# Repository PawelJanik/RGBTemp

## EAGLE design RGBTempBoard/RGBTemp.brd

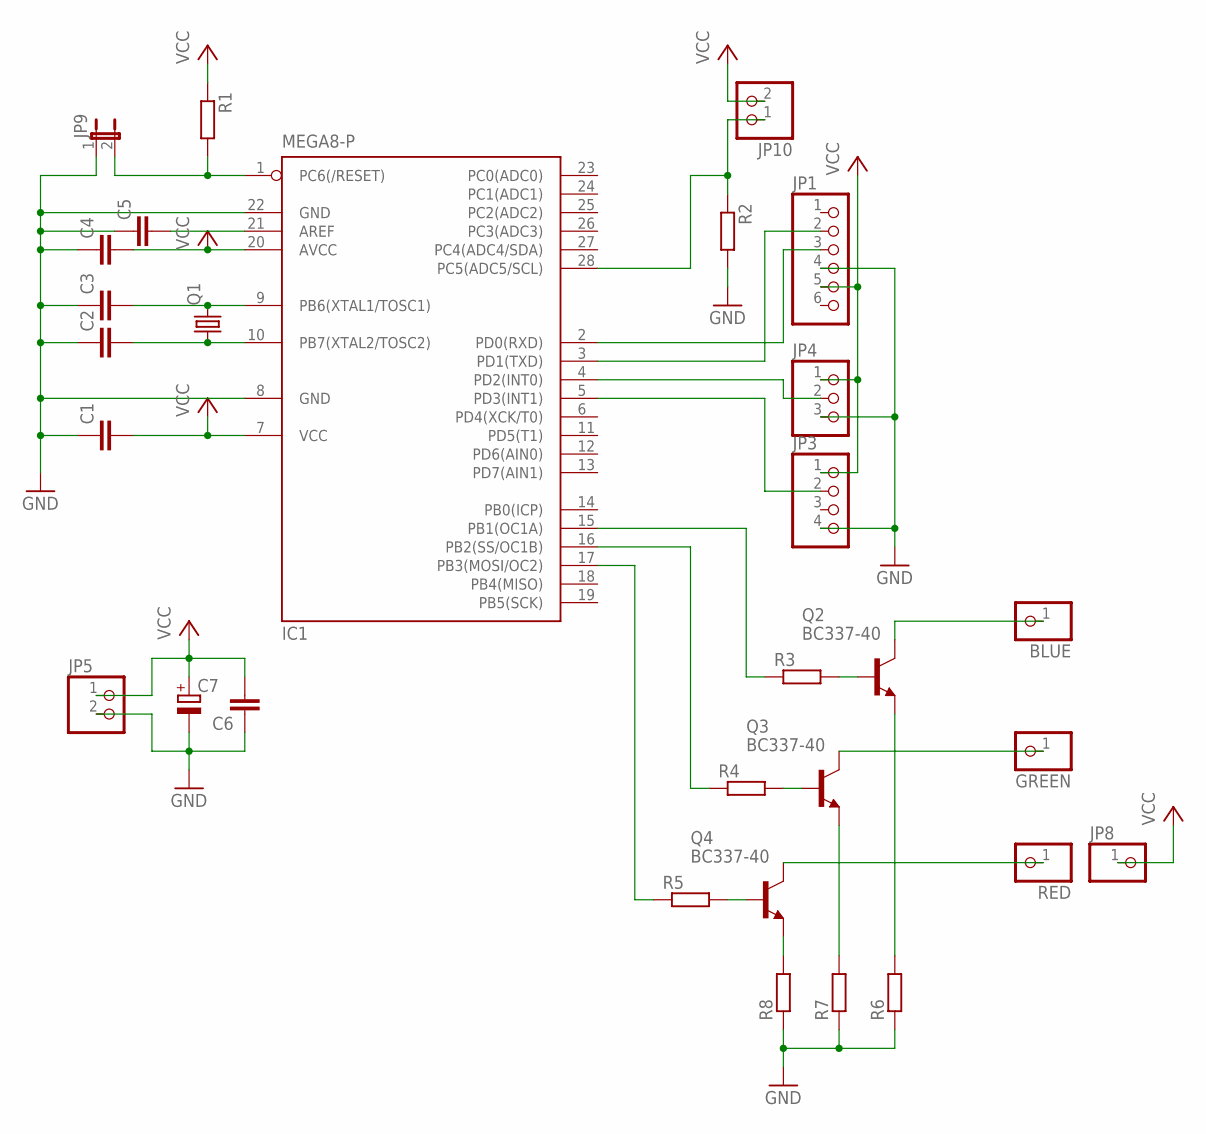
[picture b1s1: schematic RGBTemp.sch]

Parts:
BLUE: PINHD-1X1; 1X01
C1, C2, C3, C4, C5, C6: C-EU025-025X050; C025-025X050
C7: CPOL-EUE5-8.5; E5-8,5
GREEN: PINHD-1X1; 1X01
IC1: MEGA8-P; DIL28-3
JP1: PINHD-1X6; 1X06
JP3: PINHD-1X4; 1X04
JP4: PINHD-1X3; 1X03
JP5, JP10: PINHD-1X2; 1X02
JP8: PINHD-1X1; 1X01
JP9: JP1E; JP1
Q1: CRYSTALHC49U-V; HC49U-V
Q2, Q3, Q4: BC337-40; TO92
R1, R2, R3, R4, R5: R-EU_R1206; R1206
R6, R7, R8: R-EU_0207/2V; 0207/2V
RED: PINHD-1X1; 1X01

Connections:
GND: C1.1, C2.1, C3.1, C4.1, C5.1, C6.1, C7.-, IC1.8 (GND), IC1.22 (GND), JP1.4, JP3.4, JP4.3, JP5.2, JP9.1, R2.2, R6.1, R7.1, R8.1
unnamed: C2.2, IC1.10 (PB7(XTAL2/TOSC2)), Q1.1
unnamed: C3.2, IC1.9 (PB6(XTAL1/TOSC1)), Q1.2
unnamed: IC1.1 (PC6(/RESET)), JP9.2, R1.2
unnamed: C5.2, IC1.21 (AREF)
unnamed: Q4.3 (C), RED.1
unnamed: IC1.4 (PD2(INT0)), JP4.2
unnamed: IC1.5 (PD3(INT1)), JP3.2
unnamed: IC1.2 (PD0(RXD)), JP1.3
unnamed: IC1.3 (PD1(TXD)), JP1.2
unnamed: Q4.2 (B), R5.2
unnamed: Q3.2 (B), R4.2
unnamed: Q2.2 (B), R3.2
unnamed: Q2.1 (E), R6.2
unnamed: Q3.1 (E), R7.2
unnamed: Q4.1 (E), R8.2
unnamed: IC1.15 (PB1(OC1A)), R3.1
unnamed: IC1.16 (PB2(SS/OC1B)), R4.1
unnamed: IC1.17 (PB3(MOSI/OC2)), R5.1
unnamed: GREEN.1, Q3.3 (C)
unnamed: BLUE.1, Q2.3 (C)
unnamed: IC1.28 (PC5(ADC5/SCL)), JP10.1, R2.1
VCC: C1.2, C4.2, C6.2, C7.+, IC1.7 (VCC), IC1.20 (AVCC), JP1.5, JP3.1, JP4.1, JP5.1, JP8.1, JP10.2, R1.1

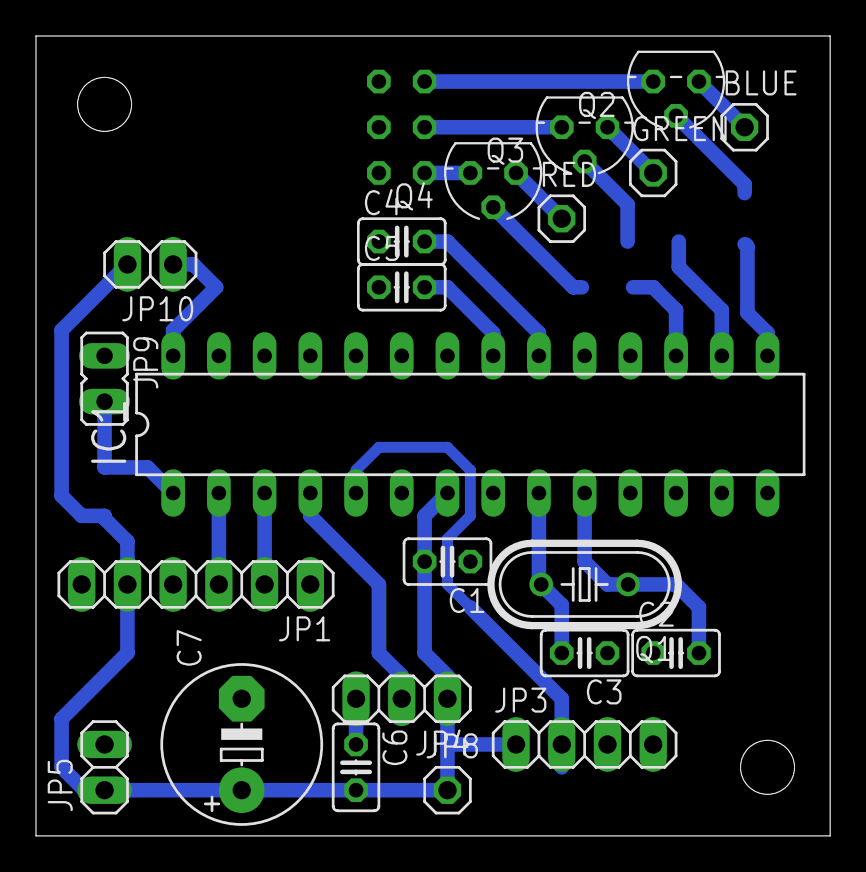
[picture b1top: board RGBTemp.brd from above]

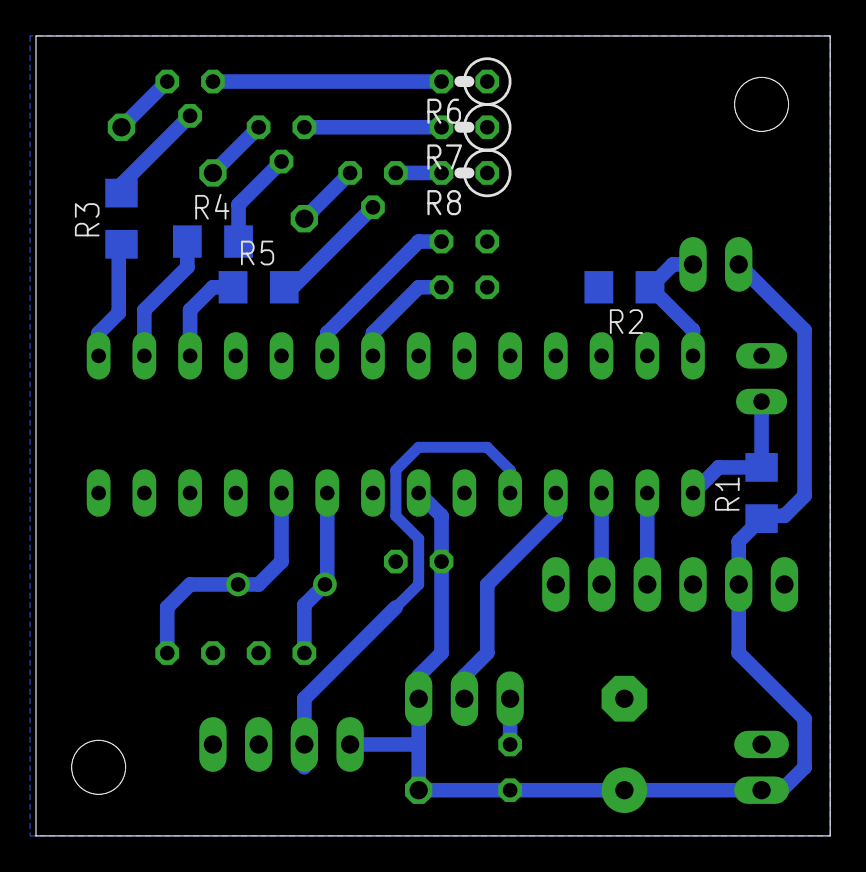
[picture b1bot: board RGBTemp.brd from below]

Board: 2 copper layers, 44.1 x 44.4 mm, 30 parts (8 on the bottom side), 23 nets.

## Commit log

2018-04-10 Update for arduino program
2018-04-17 Add RGBTempPC
    add PC program to control RGBTemp, and up date for arduino program
2018-04-17 Add Andriod app
2018-04-22 pictures and little updates
2018-04-22 Pictures update
